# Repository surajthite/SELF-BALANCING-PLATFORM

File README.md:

# SELF-BALANCING-PLATFORM-
FINAL YEAR ENGINEERING PROJECT

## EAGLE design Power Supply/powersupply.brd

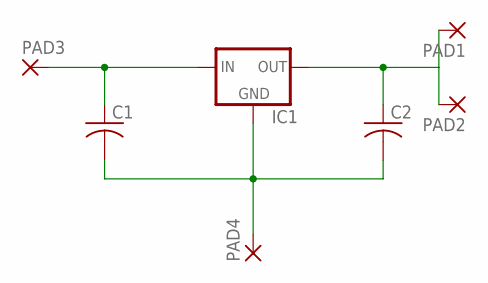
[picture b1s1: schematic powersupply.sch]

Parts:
C1, C2: C-US025-040X050; C025-040X050
IC1: 78MXXL
PAD1, PAD2, PAD3, PAD4: 2,54/1,1

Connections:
unnamed: C1.1, IC1.IN, PAD3.1
unnamed: C1.2, C2.2, IC1.GND, PAD4.1
unnamed: C2.1, IC1.OUT, PAD1.1, PAD2.1

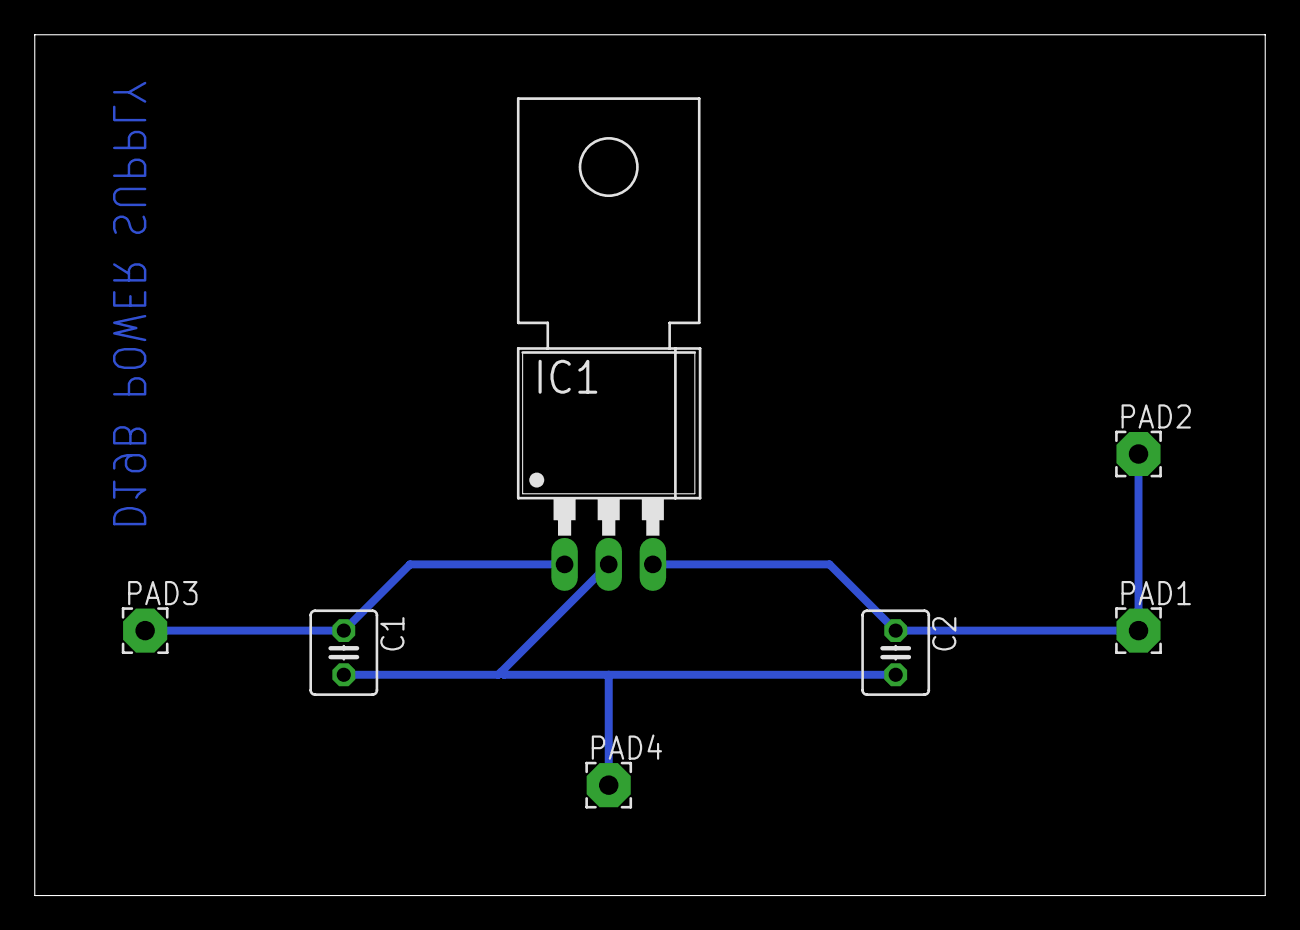
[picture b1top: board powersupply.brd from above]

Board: 2 copper layers, 70.8 x 49.5 mm, 7 parts (0 on the bottom side), 3 nets.
